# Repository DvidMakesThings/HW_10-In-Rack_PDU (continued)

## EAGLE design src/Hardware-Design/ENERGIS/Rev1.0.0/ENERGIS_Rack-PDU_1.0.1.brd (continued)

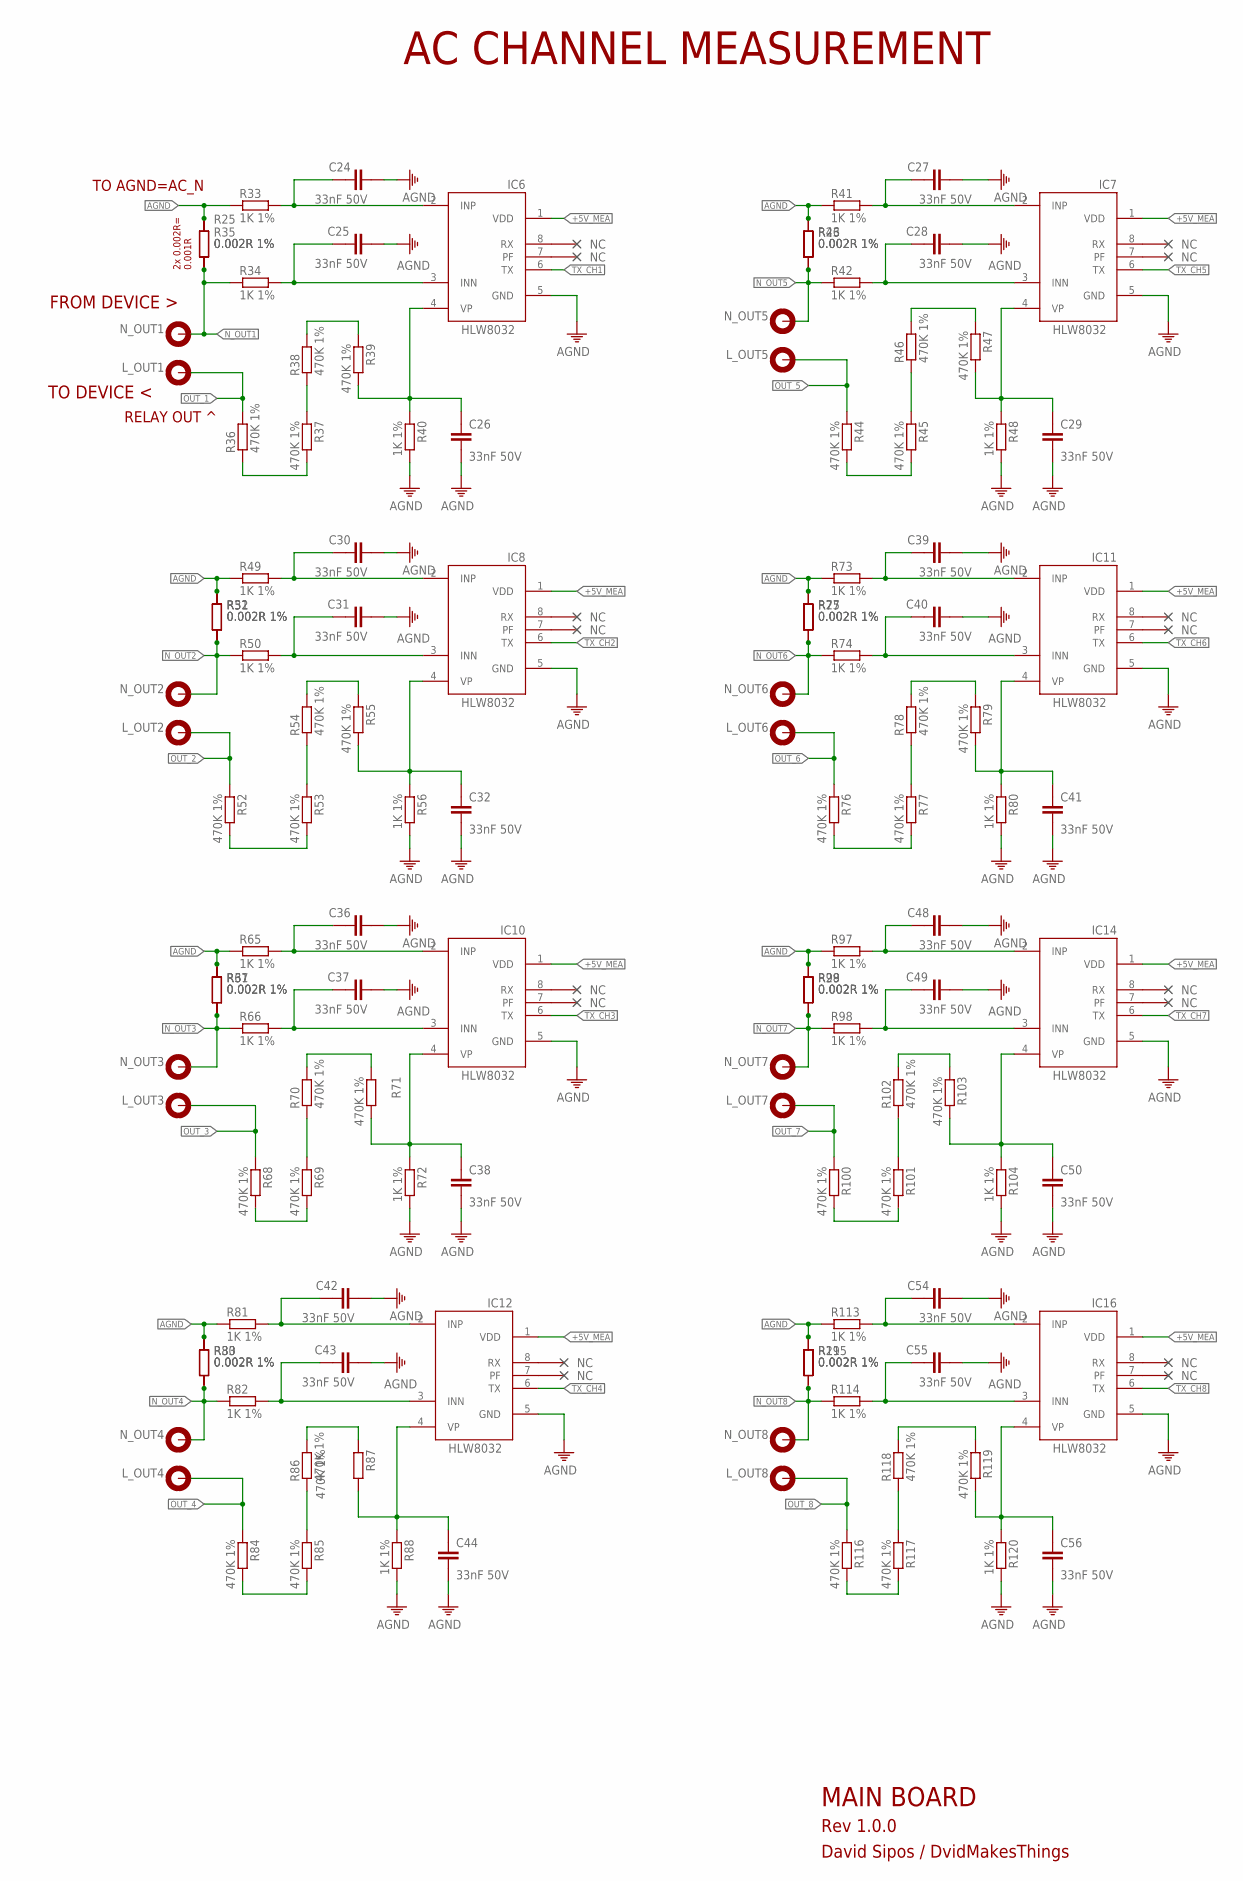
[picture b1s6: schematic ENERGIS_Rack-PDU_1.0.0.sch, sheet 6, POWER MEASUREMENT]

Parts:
C24, C25, C26, C27, C28, C29, C30, C31, C32, C36, C37, C38, C39, C40, C41, C42, C43, C44, C48, C49, C50, C54, C55, C56: 33nF 50V; 0805
IC6, IC7, IC8, IC10, IC11, IC12, IC14, IC16: HLW8032; SO8
L_OUT1, L_OUT2, L_OUT3, L_OUT4, L_OUT5, L_OUT6, L_OUT7, L_OUT8: MOUNT-PAD-ROUND2.8; 2,8-PAD
N_OUT1, N_OUT2, N_OUT3, N_OUT4, N_OUT5, N_OUT6, N_OUT7, N_OUT8: MOUNT-PAD-ROUND2.8; 2,8-PAD
R25, R26, R27, R28, R29, R30, R31, R32, R35, R43, R51, R67, R75, R83, R99, R115: 0.002R 1%; 2512
R33, R34, R40, R41, R42, R48, R49, R50, R56, R65, R66, R72, R73, R74, R80, R81, R82, R88, R97, R98, R104, R113, R114, R120: 1K 1%; 0805
R36, R37, R38, R39, R44, R45, R46, R47, R52, R53, R54, R55, R68, R69, R70, R71, R76, R77, R78, R79, R84, R85, R86, R87, R100, R101, R102, R103, R116, R117, R118, R119: 470K 1%; 0805

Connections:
+5V_MEA: IC6.1 (VDD), IC7.1 (VDD), IC8.1 (VDD), IC10.1 (VDD), IC11.1 (VDD), IC12.1 (VDD), IC14.1 (VDD), IC16.1 (VDD); also elsewhere on the board
AGND: C24.2, C25.2, C26.2, C27.2, C28.2, C29.2, C30.2, C31.2, C32.2, C36.2, C37.2, C38.2, C39.2, C40.2, C41.2, C42.2, C43.2, C44.2, C48.2, C49.2, C50.2, C54.2, C55.2, C56.2, IC6.5 (GND), IC7.5 (GND), IC8.5 (GND), IC10.5 (GND), IC11.5 (GND), IC12.5 (GND), IC14.5 (GND), IC16.5 (GND), R25.2, R26.2, R27.2, R28.2, R29.2, R30.2, R31.2, R32.2, R33.1, R35.2, R40.2, R41.1, R43.2, R48.2, R49.1, R51.2, R56.2, R65.1, R67.2, R72.2, R73.1, R75.2, R80.2, R81.1, R83.2, R88.2, R97.1, R99.2, R104.2, R113.1, R115.2, R120.2; also elsewhere on the board
unnamed: C24.1, IC6.2 (INP), R33.2
unnamed: C25.1, IC6.3 (INN), R34.2
unnamed: R38.2, R39.1
unnamed: R52.2, R53.2
unnamed: R37.1, R38.1
unnamed: C26.1, IC6.4 (VP), R39.2, R40.1
unnamed: C27.1, IC7.2 (INP), R41.2
unnamed: C28.1, IC7.3 (INN), R42.2
unnamed: R53.1, R54.1
unnamed: R54.2, R55.1
unnamed: R68.2, R69.2
unnamed: C29.1, IC7.4 (VP), R47.2, R48.1
unnamed: C30.1, IC8.2 (INP), R49.2
unnamed: C31.1, IC8.3 (INN), R50.2
unnamed: R69.1, R70.1
unnamed: R70.2, R71.1
unnamed: R84.2, R85.2
unnamed: C32.1, IC8.4 (VP), R55.2, R56.1
unnamed: C36.1, IC10.2 (INP), R65.2
unnamed: C37.1, IC10.3 (INN), R66.2
unnamed: R85.1, R86.1
unnamed: R86.2, R87.1
unnamed: R44.2, R45.2
unnamed: C38.1, IC10.4 (VP), R71.2, R72.1
unnamed: C39.1, IC11.2 (INP), R73.2
unnamed: C40.1, IC11.3 (INN), R74.2
unnamed: R45.1, R46.1
unnamed: R46.2, R47.1
unnamed: R76.2, R77.2
unnamed: C41.1, IC11.4 (VP), R79.2, R80.1
unnamed: C42.1, IC12.2 (INP), R81.2
unnamed: C43.1, IC12.3 (INN), R82.2
unnamed: R77.1, R78.1
unnamed: R78.2, R79.1
unnamed: R100.2, R101.2
unnamed: C44.1, IC12.4 (VP), R87.2, R88.1
unnamed: C48.1, IC14.2 (INP), R97.2
unnamed: C49.1, IC14.3 (INN), R98.2
unnamed: R101.1, R102.1
unnamed: R102.2, R103.1
unnamed: R116.2, R117.2
unnamed: C50.1, IC14.4 (VP), R103.2, R104.1
unnamed: C54.1, IC16.2 (INP), R113.2
unnamed: C55.1, IC16.3 (INN), R114.2
unnamed: R117.1, R118.1
unnamed: R118.2, R119.1
unnamed: C56.1, IC16.4 (VP), R119.2, R120.1
unnamed: R36.1, R37.2
N_OUT1: N_OUT1.B2,8, R25.1, R34.1, R35.1
N_OUT2: N_OUT2.B2,8, R32.1, R50.1, R51.1
N_OUT3: N_OUT3.B2,8, R31.1, R66.1, R67.1
N_OUT4: N_OUT4.B2,8, R30.1, R82.1, R83.1
N_OUT5: N_OUT5.B2,8, R26.1, R42.1, R43.1
N_OUT6: N_OUT6.B2,8, R27.1, R74.1, R75.1
N_OUT7: N_OUT7.B2,8, R28.1, R98.1, R99.1
N_OUT8: N_OUT8.B2,8, R29.1, R114.1, R115.1
OUT_1: L_OUT1.B2,8, R36.2; also elsewhere on the board
OUT_2: L_OUT2.B2,8, R52.1; also elsewhere on the board
OUT_3: L_OUT3.B2,8, R68.1; also elsewhere on the board
OUT_4: L_OUT4.B2,8, R84.1; also elsewhere on the board
OUT_5: L_OUT5.B2,8, R44.1; also elsewhere on the board
OUT_6: L_OUT6.B2,8, R76.1; also elsewhere on the board
OUT_7: L_OUT7.B2,8, R100.1; also elsewhere on the board
OUT_8: L_OUT8.B2,8, R116.1; also elsewhere on the board
TX_CH1: IC6.6 (TX); also elsewhere on the board
TX_CH2: IC8.6 (TX); also elsewhere on the board
TX_CH3: IC10.6 (TX); also elsewhere on the board
TX_CH4: IC12.6 (TX); also elsewhere on the board
TX_CH5: IC7.6 (TX); also elsewhere on the board
TX_CH6: IC11.6 (TX); also elsewhere on the board
TX_CH7: IC14.6 (TX); also elsewhere on the board
TX_CH8: IC16.6 (TX); also elsewhere on the board

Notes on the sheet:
AC CHANNEL MEASUREMENT
MAIN BOARD
Rev 1.0.0
David Sipos / DvidMakesThings
TO DEVICE <
FROM DEVICE >
2x 0.002R= 0.001R
TO AGND=AC_N
RELAY OUT ^

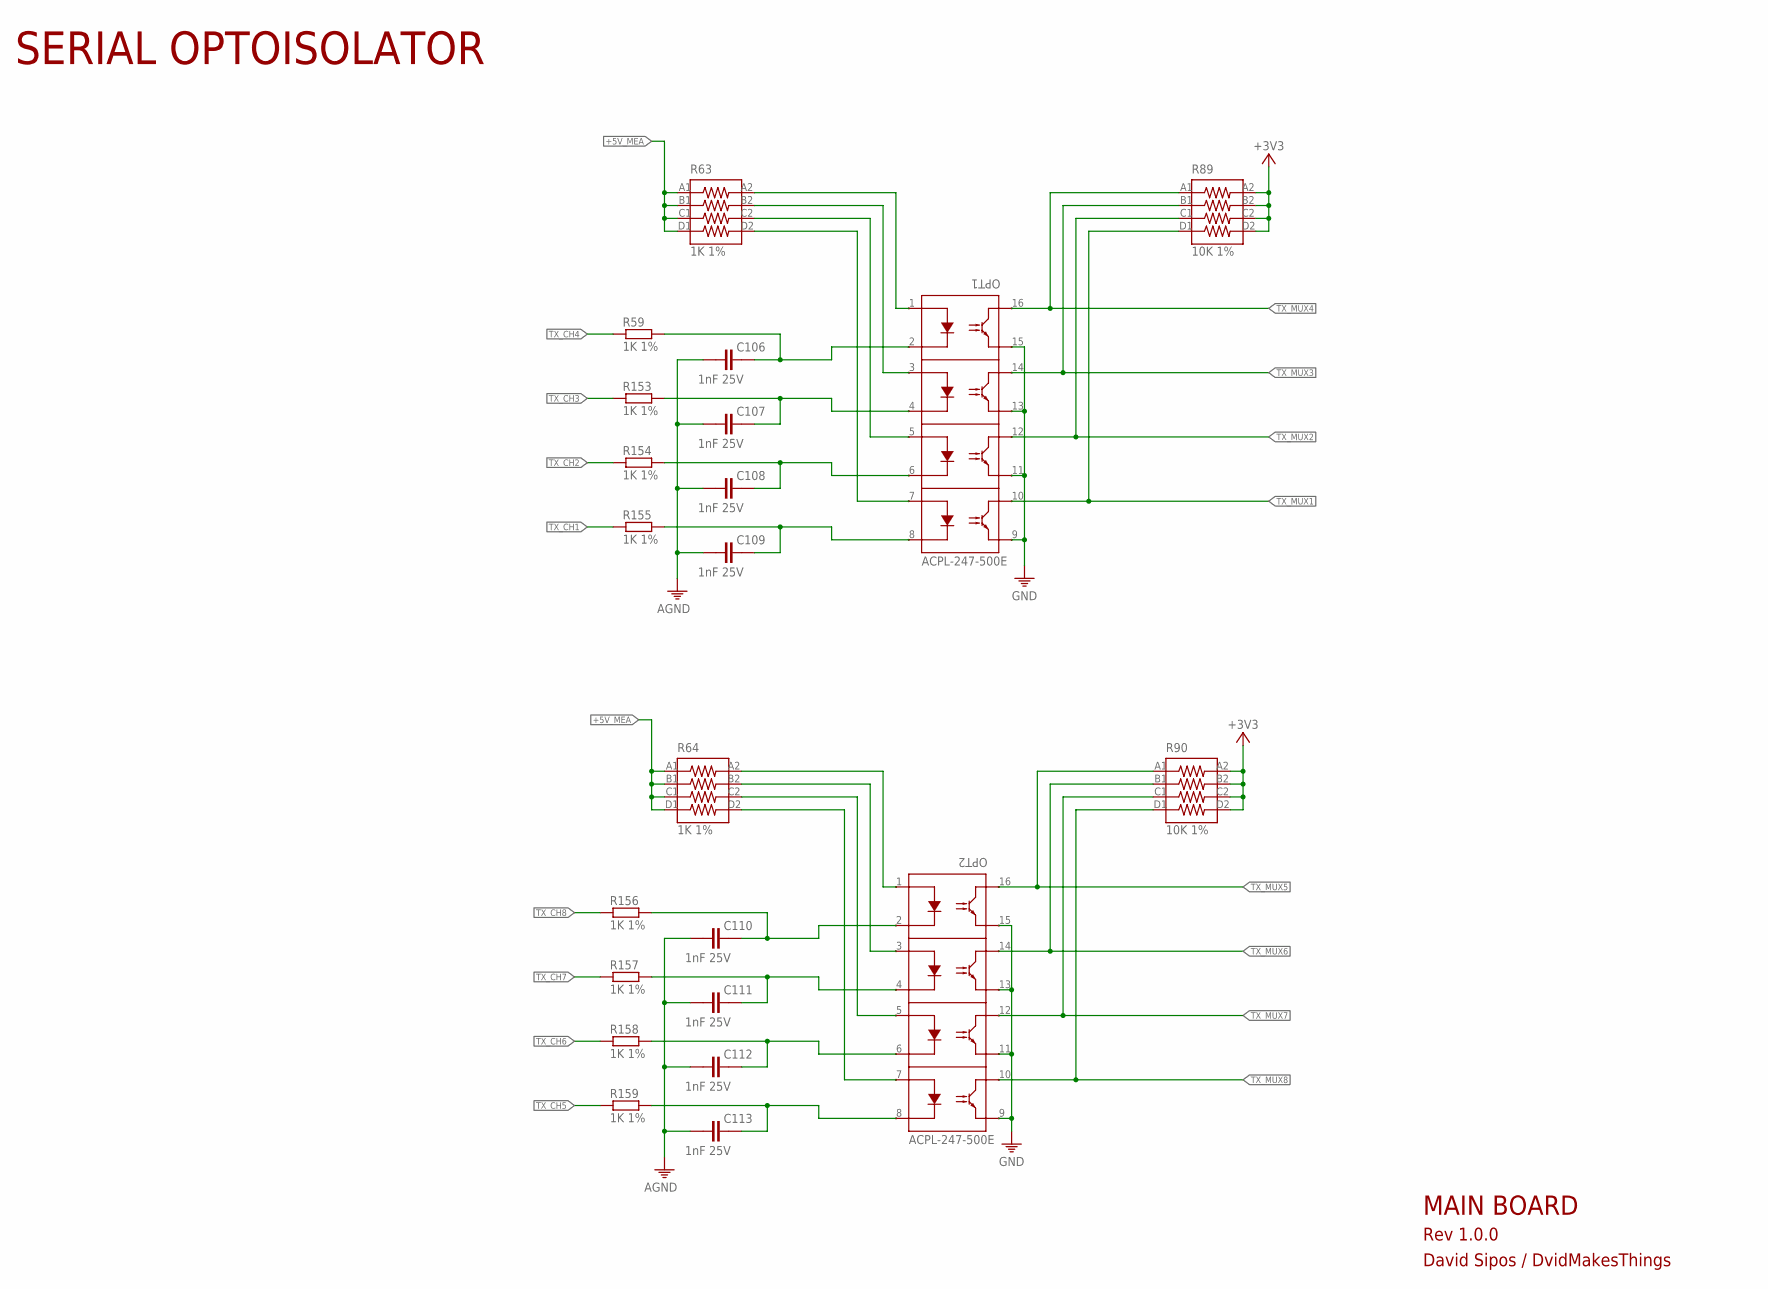
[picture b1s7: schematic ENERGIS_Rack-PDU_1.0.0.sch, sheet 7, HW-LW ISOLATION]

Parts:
C106, C107, C108, C109, C110, C111, C112, C113: 1nF 25V; 0201
OPT1, OPT2: ACPL-247-500E; SO16
R59, R153, R154, R155, R156, R157, R158, R159: 1K 1%; 0201
R63, R64: 1K 1%; _0603X4-1206
R89, R90: 10K 1%; _0603X4-1206

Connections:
+3V3: R89.A2 (8), R89.B2 (7), R89.C2 (6), R89.D2 (5), R90.A2 (8), R90.B2 (7), R90.C2 (6), R90.D2 (5); also elsewhere on the board
+5V_MEA: R63.A1 (1), R63.B1 (2), R63.C1 (3), R63.D1 (4), R64.A1 (1), R64.B1 (2), R64.C1 (3), R64.D1 (4); also elsewhere on the board
AGND: C106.2, C107.2, C108.2, C109.2, C110.2, C111.2, C112.2, C113.2; also elsewhere on the board
GND: OPT1.9, OPT1.11, OPT1.13, OPT1.15, OPT2.9, OPT2.11, OPT2.13, OPT2.15; also elsewhere on the board
TX1_LP: C109.1, OPT1.8, R155.2
TX1_PU: OPT1.7, R63.D2 (5)
TX2_LP: C108.1, OPT1.6, R154.2
TX2_PU: OPT1.5, R63.C2 (6)
TX3_LP: C107.1, OPT1.4, R153.2
TX3_PU: OPT1.3, R63.B2 (7)
TX4_LP: C106.1, OPT1.2, R59.2
TX4_PU: OPT1.1, R63.A2 (8)
TX5_LP: C110.1, OPT2.2, R156.2
TX5_PU: OPT2.1, R64.A2 (8)
TX6_LP: C111.1, OPT2.4, R157.2
TX6_PU: OPT2.3, R64.B2 (7)
TX7_LP: C112.1, OPT2.6, R158.2
TX7_PU: OPT2.5, R64.C2 (6)
TX8_LP: C113.1, OPT2.8, R159.2
TX8_PU: OPT2.7, R64.D2 (5)
TX_CH1: R155.1; also elsewhere on the board
TX_CH2: R154.1; also elsewhere on the board
TX_CH3: R153.1; also elsewhere on the board
TX_CH4: R59.1; also elsewhere on the board
TX_CH5: R159.1; also elsewhere on the board
TX_CH6: R158.1; also elsewhere on the board
TX_CH7: R157.1; also elsewhere on the board
TX_CH8: R156.1; also elsewhere on the board
TX_MUX1: OPT1.10, R89.D1 (4); also elsewhere on the board
TX_MUX2: OPT1.12, R89.C1 (3); also elsewhere on the board
TX_MUX3: OPT1.14, R89.B1 (2); also elsewhere on the board
TX_MUX4: OPT1.16, R89.A1 (1); also elsewhere on the board
TX_MUX5: OPT2.16, R90.A1 (1); also elsewhere on the board
TX_MUX6: OPT2.14, R90.B1 (2); also elsewhere on the board
TX_MUX7: OPT2.12, R90.C1 (3); also elsewhere on the board
TX_MUX8: OPT2.10, R90.D1 (4); also elsewhere on the board

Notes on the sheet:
MAIN BOARD
Rev 1.0.0
David Sipos / DvidMakesThings
SERIAL OPTOISOLATOR

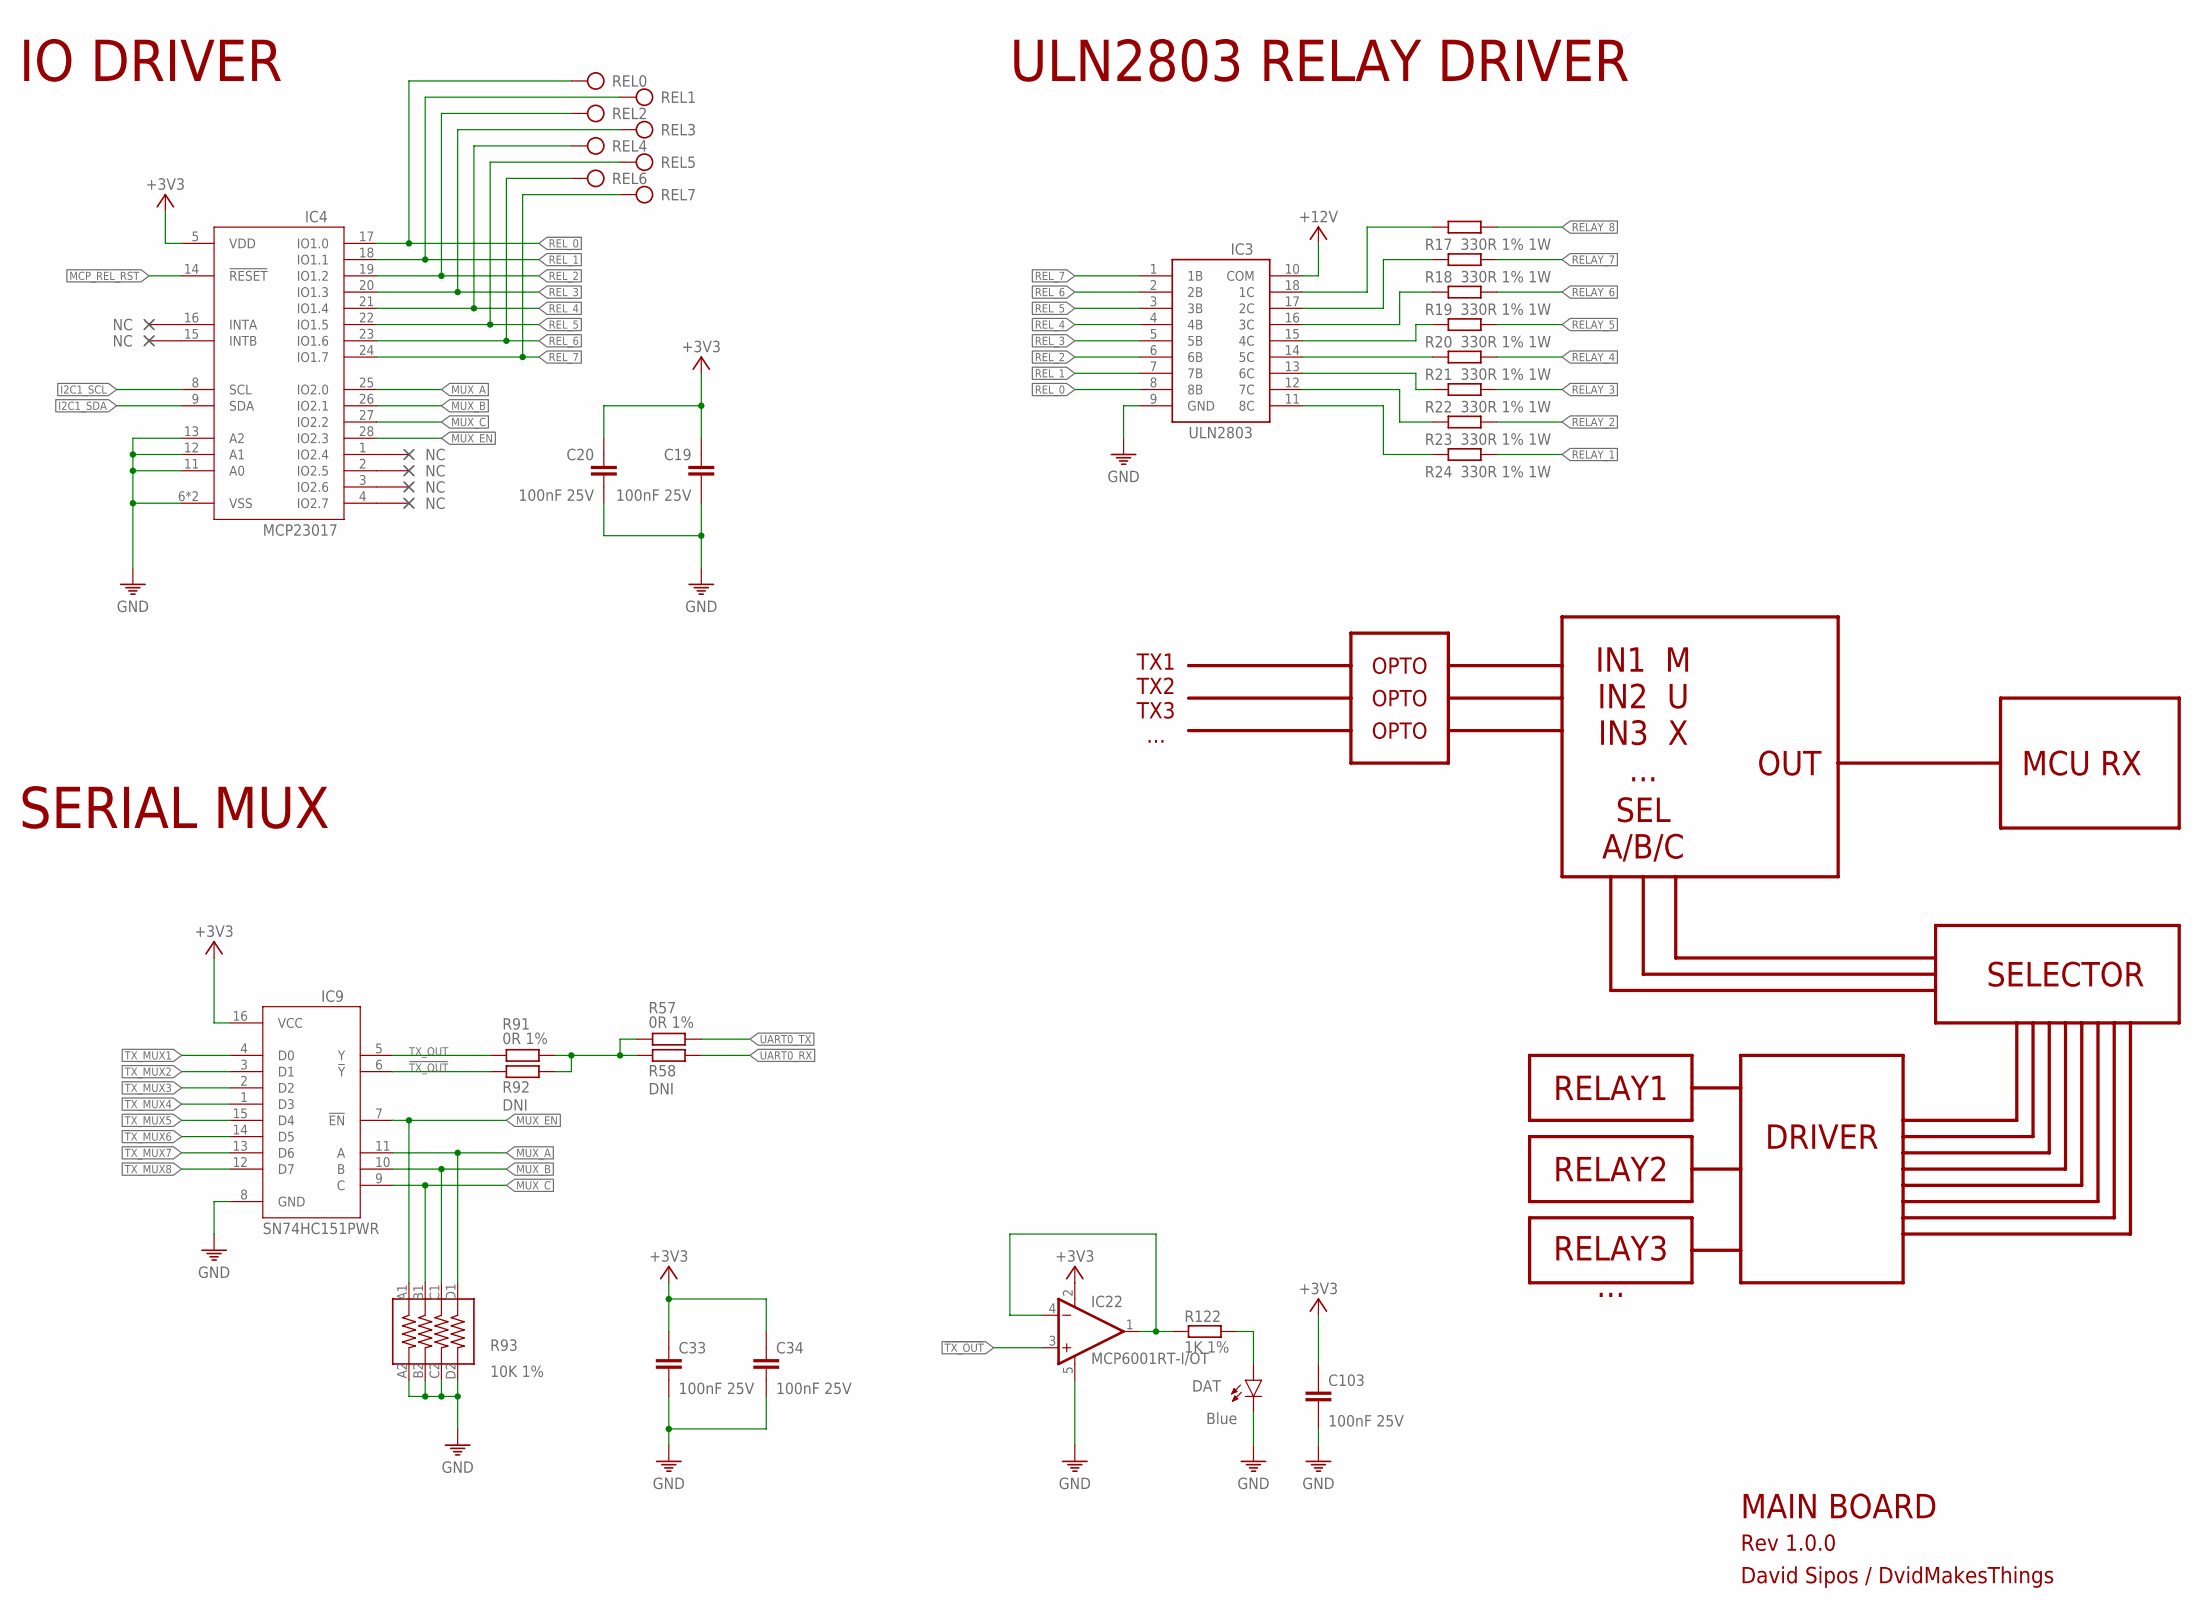
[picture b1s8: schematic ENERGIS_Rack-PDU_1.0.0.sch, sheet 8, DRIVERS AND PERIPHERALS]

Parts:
C19, C20, C33, C34: 100nF 25V; 0402
C103: 100nF 25V; 0201
DAT: Blue; LED-0603
IC3: ULN2803AFWG; SO18
IC4: MCP23017T-E/ML; QFN28[6X6]ML
IC9: SN74HC151PWR; TSSOP16
IC22: MCP6001RT-I/OT; SOT23-5
R17, R18, R19, R20, R21, R22, R23, R24: 330R 1% 1W; 2512
R57, R91: 0R 1%; 0402
R58, R92: DNI; 0402
R93: 10K 1%; _0603X4-1206
R122: 1K 1%; 0402
REL0, REL1, REL2, REL3, REL4, REL5, REL6, REL7: TP

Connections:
!TX_OUT: IC9.6 (!Y), IC22.3 (+IN), R92.1
+3V3: C19.1, C20.1, C33.1, C34.1, C103.1, IC4.5 (VDD), IC9.16 (VCC), IC22.2 (V+); also elsewhere on the board
+12V: IC3.10 (COM); also elsewhere on the board
GND: C19.2, C20.2, C33.2, C34.2, C103.2, DAT.C, IC3.9 (GND), IC4.6 (VSS), IC4.11 (A0), IC4.12 (A1), IC4.13 (A2), IC4.PAD (VSS), IC9.8 (GND), IC22.5 (V-), R93.A2 (8), R93.B2 (7), R93.C2 (6), R93.D2 (5); also elsewhere on the board
I2C1_SCL: IC4.8 (SCL); also elsewhere on the board
I2C1_SDA: IC4.9 (SDA); also elsewhere on the board
MCP_REL_RST: IC4.14 (!RESET); also elsewhere on the board
MUX_A: IC4.25 (IO2.0), IC9.11 (A), R93.D1 (4)
MUX_B: IC4.26 (IO2.1), IC9.10 (B), R93.C1 (3)
MUX_C: IC4.27 (IO2.2), IC9.9 (C), R93.B1 (2)
MUX_EN: IC4.28 (IO2.3), IC9.7 (!EN), R93.A1 (1)
unnamed: DAT.A, R122.2
unnamed: IC3.14 (5C), R21.1
unnamed: IC3.11 (8C), R24.1
unnamed: IC3.12 (7C), R23.1
unnamed: IC3.13 (6C), R22.1
unnamed: IC3.15 (4C), R20.1
unnamed: IC3.16 (3C), R19.1
unnamed: IC3.17 (2C), R18.1
unnamed: IC3.18 (1C), R17.1
RELAY_1: R24.2; also elsewhere on the board
RELAY_2: R23.2; also elsewhere on the board
RELAY_3: R22.2; also elsewhere on the board
RELAY_4: R21.2; also elsewhere on the board
RELAY_5: R20.2; also elsewhere on the board
RELAY_6: R19.2; also elsewhere on the board
RELAY_7: R18.2; also elsewhere on the board
RELAY_8: R17.2; also elsewhere on the board
REL_0: IC3.8 (8B), IC4.17 (IO1.0), REL0.TP
REL_1: IC3.7 (7B), IC4.18 (IO1.1), REL1.TP
REL_2: IC3.6 (6B), IC4.19 (IO1.2), REL2.TP
REL_3: IC3.5 (5B), IC4.20 (IO1.3), REL3.TP
REL_4: IC3.4 (4B), IC4.21 (IO1.4), REL4.TP
REL_5: IC3.3 (3B), IC4.22 (IO1.5), REL5.TP
REL_6: IC3.2 (2B), IC4.23 (IO1.6), REL6.TP
REL_7: IC3.1 (1B), IC4.24 (IO1.7), REL7.TP
TX_FB: IC22.1 (OUT), IC22.4 (-IN), R122.1
TX_MUX1: IC9.4 (D0); also elsewhere on the board
TX_MUX2: IC9.3 (D1); also elsewhere on the board
TX_MUX3: IC9.2 (D2); also elsewhere on the board
TX_MUX4: IC9.1 (D3); also elsewhere on the board
TX_MUX5: IC9.15 (D4); also elsewhere on the board
TX_MUX6: IC9.14 (D5); also elsewhere on the board
TX_MUX7: IC9.13 (D6); also elsewhere on the board
TX_MUX8: IC9.12 (D7); also elsewhere on the board
TX_OUT: IC9.5 (Y), R91.1
TX_OUTSEL: R57.1, R58.1, R91.2, R92.2
UART0_RX: R58.2; also elsewhere on the board
UART0_TX: R57.2; also elsewhere on the board

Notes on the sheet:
ULN2803 RELAY DRIVER
IO DRIVER
SERIAL MUX
MAIN BOARD
Rev 1.0.0
David Sipos / DvidMakesThings
TX1 TX2 TX3 ...
OPTO
IN1 M IN2 U IN3 X ...
SELECTOR
SEL A/B/C
OUT
MCU RX
RELAY1
RELAY2
RELAY3 ...
DRIVER

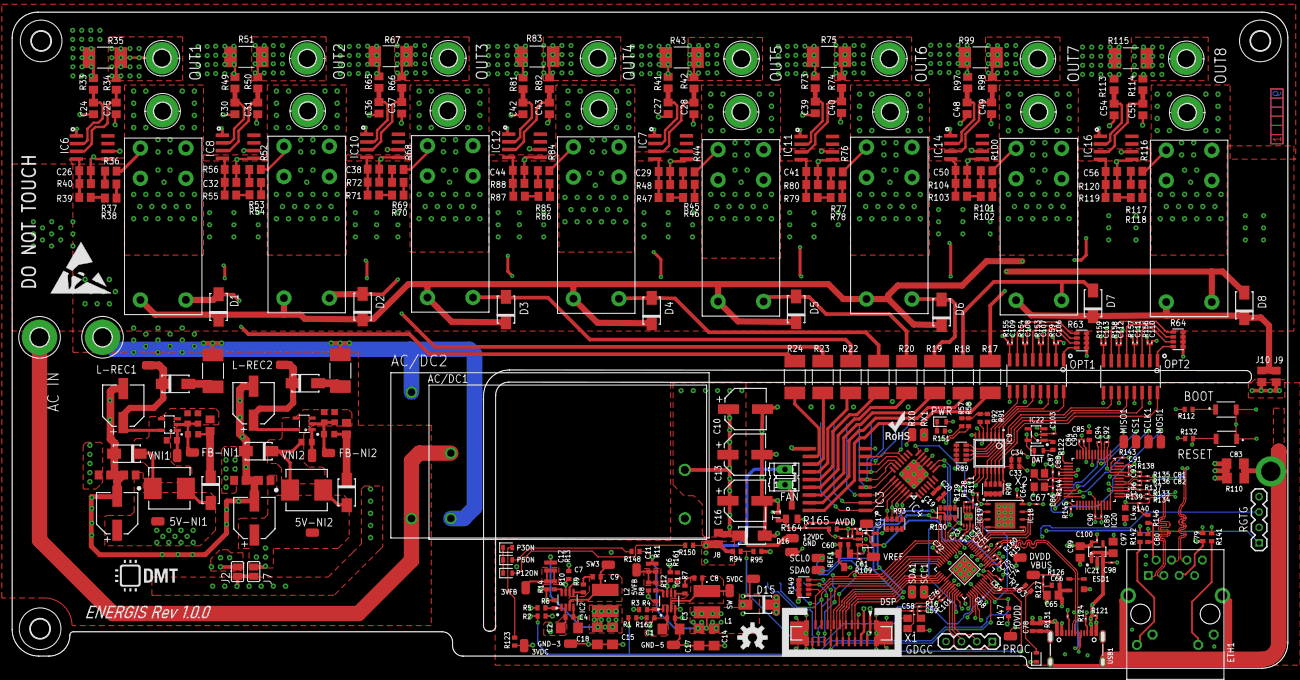
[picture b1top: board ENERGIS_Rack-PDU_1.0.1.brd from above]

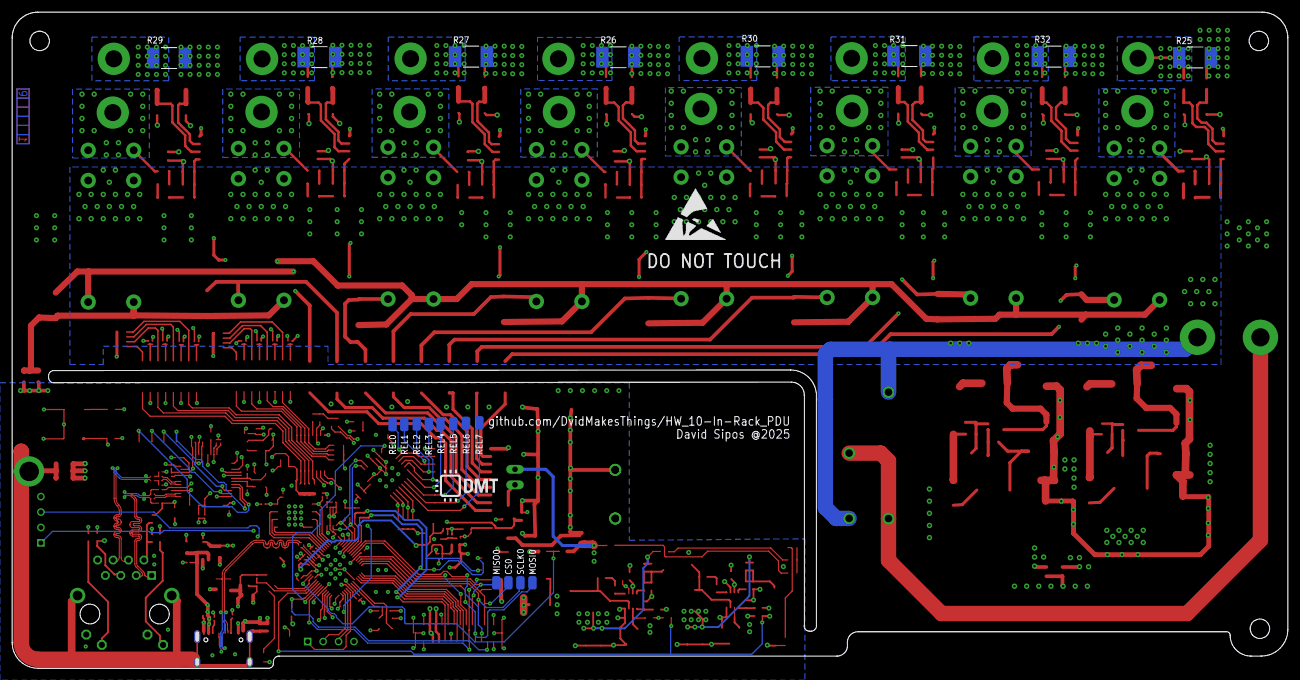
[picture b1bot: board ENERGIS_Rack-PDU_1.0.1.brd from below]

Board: 6 copper layers, 210.0 x 108.0 mm, 428 parts (22 on the bottom side), 251 nets.

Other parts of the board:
U$1, U$2: ESD_10.00
U$3, U$4, U$6: 3,2
U$5, U$7: DMT
U$10: OSHW-LOGO-M
U$11: ROHS_LOGO_0.18_IN

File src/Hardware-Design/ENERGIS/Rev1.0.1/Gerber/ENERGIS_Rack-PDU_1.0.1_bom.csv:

Comment,Designator,Footprint,LCSC Part #
0.002R 1%,R25 R26 R27 R28 R29 R30 R31 R32 R35 R43 R51 R67 R75 R83 R99 R115,2512,C728320
0R 1%,J8 J9 J10,0805,C17477
0R 1%,R57 R91,0402,C17168
1K 1%,R16,0201,C270365
1K 1%,R33 R34 R40 R41 R42 R48 R49 R50 R56,0805,C17513
1K 1%,R59,0201,C270365
1K 1%,R63 R64,_0603X4-1206,C110021
1K 1%,R65 R66 R72 R73 R74 R80 R81 R82 R88 R97 R98 R104,0805,C17513
1K 1%,R112,0402,C11702
1K 1%,R113 R114 R120,0805,C17513
1K 1%,R122 R123 R151,0402,C11702
1K 1%,R153 R154 R155 R156 R157 R158 R159,0201,C270365
1K 1%,R163,0402,C11702
1M 1%,R110,1206,C17927
1M 1%,R131,0402,C26083
1M 1%,R144,0201,C295786
1N4007,D9 D10 D12 D13,SMA/DO-214AC,C727081
1mH,L3 L5,L-6.6X6.6,C168049
1nF 25V,C106 C107 C108 C109 C110 C111 C112 C113,0201,C7694325V
1nF 50V,C5 C51,0603,C1588
1uF 16V,C102,0201,C307385
1uF 25V,C60 C104,0402,C52923
1uF 50V,C45 C57,0805,C28323
2.2K 1%,R121,0201,C473508
2.2uF 50V,C21 C46,0603,C913904
2.2uF 400V,C35 C47,6.3X7.7(DXL),C3345109
2.4K 1%,R148,0402,C25882
3.3K 1%,R130 R149,_0603X4-1206,C1734380
3.3R 1%,R133 R134 R135 R136,0201,C158547
4.2uH,L2,SRR5228A,
4.7K 1%,R109 R129 R145,0201,C270346
4.7nF 50V,C78,0402,C1538
4.7uF 25V,C85,0402,C22367824
4.9uH,L1,SRR5228A,
4.99K 1%,R60 R61 R105 R107,0603,C23046
5.1K 1%,R124 R125,0201,C274341
6.8nF 50V,C81 C82,0201,C285015
7.5K 1%,R6 R12,0402,C25918
8.2K 1%,R150,0402,C25924
9.09K 1%,R4,0402,C11549
10K 1%,R2,0402,C25744
10K 1%,R89 R90 R93,_0603X4-1206,C110924
10K 1%,R95,0402,C25744
10K 1%,R96 R108,0805,C17414
10K 1%,R126 R127,0201,C473048
10K 1%,R132 R147 R162 R164,0402,C25744
10R 1%,R7 R9,0402,C25077
10R 1%,R152,0201,C270817
10uF 50V,C65 C97 C99,0805,C440198
12.4K 1%,R143,R0201,
12.7K 1%,R14,0402,C25853
15pF 50V,C58 C59,0201,C22374851
18pF 50V,C86 C87,0201,C62164
20K 1%,R8,0402,C25765
22nF 50V,C80,0402,C1532
22uF 25V,C1 C2 C14 C15 C17 C18,1206,C12891
25MHz,X2,WE-XTAL_CFPX-180,C9006
27R 1%,R15 R160,0201,C473051
33K,R10,0402,
33nF 50V,C24 C25 C26 C27 C28 C29 C30 C31 C32 C36 C37 C38 C39 C40 C41 C42 C43 C44 C48 C49 C50 C54 C55 C56,0805,C107150
33pF 50V,C11 C12,0402,C107005
39R 1% 2W,R62 R106,2512,C175263
40.2K 1%,R11 R13,0402,C25893
49.9R 1%,R137 R138 R139 R140,0201,C155744
100K 1%,R3 R5 R94,0402,C25741
100nF 25V,C3 C4 C6 C7 C8 C9 C19 C20 C33 C34,0402,C56392
100nF 25V,C61 C62 C63 C64,0201,C76939
100nF 25V,C66,0402,C56392
100nF 25V,C67 C68 C69 C70 C71 C72 C73 C74 C75 C76 C77,0201,C76939
100nF 25V,C79,0402,C56392
100nF 25V,C84 C88 C89 C90 C91 C92 C93 C94 C95 C96 C98 C100 C101 C103,0201,C76939
100uF 25V,C10 C13 C16,6.3X7.7(DXL),C267469
100uF 50V,C23 C53,6.3X7.7(DXL),C3151829
220nF 50V,C22 C52,0805,C5378
330R 1% 1W,R17 R18 R19 R20 R21 R22 R23 R24,2512,C620880
470K 1%,R36 R37 R38 R39 R44 R45 R46 R47 R52 R53 R54 R55 R68 R69 R70 R71 R76 R77 R78 R79 R84 R85 R86 R87 R100 R101 R102 R103 R116 R117 R118 R119,0805,C17709
470R 1%,R141 R142 R146,0402,C25117
ABM8-272-T3 12MHz,X1,WE-XTAL_CFPX-180,C20625731
ACPL-247-500E ,OPT1 OPT2,SO16,C188681
AFC11-S20ICC-00 ,DSP,FPC20,C11073
B3U-1000P ,BOOT RESET,B3U-1000P,C231329
BLM18EG221TN1D,L4,0603,C113025
Blue,DAT,LED-0603,C965807
C1206C102KGRACTM,C83,C1206,
CAT24C256HU4IGT3,IC19,SON50P300X200X50-9T130X140N,C233771
DNI,R1 R58 R92,0402,
DNI,R111,R0201,
DNI,R161,0402,
G2RL-1A-E DC12 ,K1 K2 K3 K4 K5 K6 K7 K8,RELAY_G2RL-1A-E_DC5_OMR,C1564126
Green,P3ON P5ON P12ON PROC PWR,LED-0603,C965804
HLW8032,IC6 IC7 IC8 IC10 IC11 IC12 IC14 IC16,SO8,C128023
IRM-10-15 ,AC/DC2,IRM_15_12,C5439799
IRM_10_12,AC/DC1,IRM_10_12,C20618065
J1B1211CCD,ETH1,J1B1211CCD,C910371
JP,J2 J7,SJ,
LM4040B30FTA,REF1,SOT23,C460604
MBRA340T3G,D1 D2 D3 D4 D5 D6 D7 D8,SMA/DO-214AC,C26178
MCP6001RT-I/OT,IC17 IC22,SOT23-5,C154973
MCP23017T-E/ML ,IC4,QFN28[6X6]ML,C629439
MIC5504-3.3YM5 ,IC21,SOT23-5,C41348078
MOUNT-PAD-ROUND2.8,L_OUT1,2 8-PAD,
MOUNT-PAD-ROUND2.8,L_OUT2,2 8-PAD,
MOUNT-PAD-ROUND2.8,L_OUT3,2 8-PAD,
MOUNT-PAD-ROUND2.8,L_OUT4,2 8-PAD,
MOUNT-PAD-ROUND2.8,L_OUT5,2 8-PAD,
MOUNT-PAD-ROUND2.8,L_OUT6,2 8-PAD,
MOUNT-PAD-ROUND2.8,L_OUT7,2 8-PAD,
MOUNT-PAD-ROUND2.8,L_OUT8,2 8-PAD,
MOUNT-PAD-ROUND2.8,N_OUT1,2 8-PAD,
MOUNT-PAD-ROUND2.8,N_OUT2,2 8-PAD,
MOUNT-PAD-ROUND2.8,N_OUT3,2 8-PAD,
MOUNT-PAD-ROUND2.8,N_OUT4,2 8-PAD,
MOUNT-PAD-ROUND2.8,N_OUT5,2 8-PAD,
MOUNT-PAD-ROUND2.8,N_OUT6,2 8-PAD,
MOUNT-PAD-ROUND2.8,N_OUT7,2 8-PAD,
MOUNT-PAD-ROUND2.8,N_OUT8,2 8-PAD,
MOUNT-PAD-ROUND3.0,AC_L,3 0-PAD,
MOUNT-PAD-ROUND3.0,AC_N,3 0-PAD,
MP150GJ,IC5 IC13,SOT23-5,
MP2315GJ-Z ,IC1 IC2,SOT65P280X110-8N,C45889
NC,R128 R165,R0201,
RP2040,IC15,QFN56,C2040
SMAJ15A,D16,SMA/DO-214AC,C23424
SN74HC151PWR,IC9,TSSOP16,C2653837
SP0503BAHTG,ESD1,SOT143,C3040626
SS12,D15,SMA/DO-214AC,C727049
TP,3VDC 3VFB 5V-NI1 5V-NI2 5VDC 5VFB 12VDC AVDD CS0 CS1 DVDD FB-NI1 FB-NI2 GND GND-3 GND-5 IOVDD L-REC1 L-REC2 MISO0 MISO1 MOSI0 MOSI1 REL0 REL1 REL2 REL3 REL4 REL5 REL6 REL7 RX0 RX1 SCL0 SCL1 SCLK0 SCLK1 SDA0 SDA1 SW SW3 VBUS VNI1 VNI2 VREF,TP,
ULN2803AFWG,IC3,SO18,C845537
US1J-E3/61T ,D11 D14,SMA/DO-214AC,C44763
USB-TYPE-C-018 ,USB1,USB-C,C2927038
W25Q128JVPIQ,IC18,SON127P600X500X75-8N,C190862
W5500,IC20,LQFP48,C32843

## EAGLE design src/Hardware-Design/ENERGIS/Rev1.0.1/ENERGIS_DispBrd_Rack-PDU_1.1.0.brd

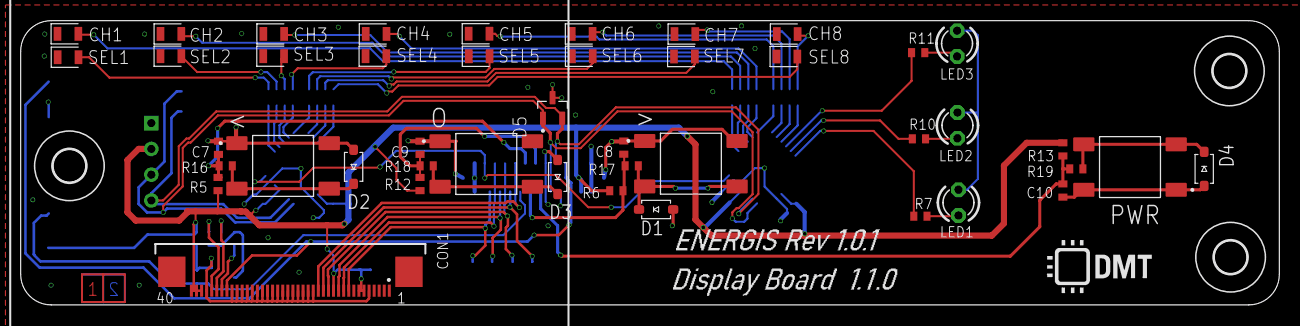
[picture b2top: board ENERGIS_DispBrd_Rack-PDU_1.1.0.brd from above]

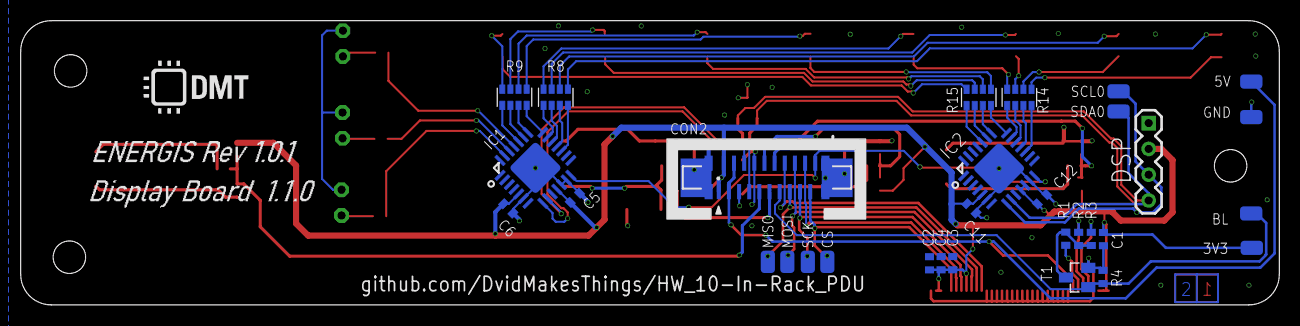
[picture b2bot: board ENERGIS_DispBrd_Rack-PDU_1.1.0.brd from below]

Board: 2 copper layers, 124.0 x 28.0 mm, 80 parts (32 on the bottom side), 63 nets.

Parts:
3V3, 5V: TP
<: TS-1002S-04326C; PUSHBUTTON-6X6
>: TS-1002S-04326C; PUSHBUTTON-6X6
BL: TP
C1, C2, C3, C4: DNI; C0402
C5, C6, C7, C8, C9, C10, C11, C12: 100nF 50V; 0402
CH1, CH2, CH3, CH4, CH5, CH6, CH7, CH8: Green; LED-0805
CON1: DNI; FPC40_3.5TFT
CON2: AFC11-S20ICC-00; FPC20
CS: TP
D1, D2, D3, D4: PTVS3V3S1UR,115; SOD-123
D5: RCLAMP0582BQTCT; SOT-523
DSP: DNI; 1X4
GND: TP
IC1, IC2: MCP23017T-E/ML; QFN28[6X6]ML
LED1: GREEN; LED3MM
LED2: BLUE; LED3MM
LED3: RED; LED3MM
MISO: TP
MOSI: TP
O: TS-1002S-04326C; PUSHBUTTON-6X6
PWR: TS-1002S-04326C; PUSHBUTTON-6X6
R1, R2, R3: DNI; 0402
R4, R16, R17, R18, R19: 10K 1%; 0402
R5, R6, R12, R13: 33K 1%; 0402
R7, R10, R11: 1K 1%; 0402
R8, R9, R14, R15: 1K 1%; _0603X4-1206
SCK: TP
SCL0: TP
SDA0: TP
SEL1, SEL2, SEL3, SEL4, SEL5, SEL6, SEL7, SEL8: Orange; LED-0805
T1: BSS138; SOT23
U$1, U$5: DMT
U$2, U$3, U$4: 3,2

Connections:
+3V3: 3V3.TP, C1.1, C2.1, C3.1, C4.1, C5.1, C6.1, C11.1, C12.1, CON1.6, CON1.7, CON1.12, CON1.38, CON1.39, CON1.40, CON2.1, CON2.2, DSP.2, IC1.5, IC1.11, IC2.5, IC2.11, IC2.12, R5.1, R6.1, R12.1, R13.1
+5V: 5V.TP, CON1.33, CON2.3, CON2.4
GND: <.1, <.2, >.1, >.2, C1.2, C2.2, C3.2, C4.2, C5.2, C6.2, C7.2, C8.2, C9.2, C10.2, C11.2, C12.2, CH1.C, CH2.C, CH3.C, CH4.C, CH5.C, CH6.C, CH7.C, CH8.C, CON1.5, CON1.16, CON1.17, CON1.18, CON1.19, CON1.20, CON1.21, CON1.22, CON1.23, CON1.24, CON1.25, CON1.26, CON1.27, CON1.28, CON1.29, CON1.30, CON1.31, CON1.32, CON1.37, CON1.Z1, CON1.Z2, CON2.5, CON2.8, CON2.Z0, CON2.Z1, CON2.Z2, CON2.Z3, CON2.Z4, CON2.Z5, D1.A, D2.A, D3.A, D4.A, D5.3, DSP.1, GND.TP, IC1.6, IC1.12, IC1.13, IC1.PAD, IC2.6, IC2.13, IC2.PAD, LED1.K, LED2.K, LED3.K, O.1, O.2, PWR.1, PWR.2, R4.2, SEL1.C, SEL2.C, SEL3.C, SEL4.C, SEL5.C, SEL6.C, SEL7.C, SEL8.C, T1.2
I2C0_SCL: CON2.7, D5.1, DSP.3, IC1.8, IC2.8, SCL0.TP
I2C0_SDA: CON2.6, D5.2, DSP.4, IC1.9, IC2.9, SDA0.TP
KEY_0: C7.1, CON2.12, R5.2, R16.2
KEY_1: C8.1, CON2.11, R6.2, R17.2
KEY_2: C9.1, CON2.10, R12.2, R18.2
KEY_3: C10.1, CON2.9, R13.2, R19.2
LCD_BL: BL.TP, CON2.13, R4.1, T1.1
LCD_CS: CON1.9, CON2.19, CS.TP
LCD_DC: CON1.10, CON2.18
LCD_MISO: CON1.14, CON2.15, MISO.TP
LCD_MOSI: CON1.13, CON2.16, MOSI.TP
LCD_RES: CON1.15, CON2.14
LCD_SCLK: CON1.11, CON2.17, SCK.TP
MCP_LCD_RST: CON2.20, IC1.14, IC2.14
unnamed: CON1.35, R2.2
unnamed: CON1.36, R3.2
unnamed: R1.1, R2.1, R3.1, T1.3
unnamed: CON1.34, R1.2
unnamed: <.3, <.4, D2.C, R16.1
unnamed: IC2.17, R14.D1
unnamed: IC2.18, R14.C1
unnamed: IC2.19, R14.B1
unnamed: IC2.20, R14.A1
unnamed: IC2.21, R15.D1
unnamed: IC2.22, R15.C1
unnamed: IC2.23, R15.B1
unnamed: IC2.24, R15.A1
unnamed: R14.D2, SEL1.A
unnamed: R14.C2, SEL2.A
unnamed: R14.B2, SEL3.A
unnamed: R14.A2, SEL4.A
unnamed: R15.D2, SEL5.A
unnamed: R15.C2, SEL6.A
unnamed: R15.B2, SEL7.A
unnamed: R15.A2, SEL8.A
unnamed: D3.C, O.3, O.4, R18.1
unnamed: D4.C, PWR.3, PWR.4, R19.1
unnamed: >.3, >.4, D1.C, R17.1
unnamed: IC1.26, R10.1
unnamed: IC1.27, R7.1
unnamed: IC1.25, R11.1
unnamed: IC1.17, R8.D1
unnamed: IC1.18, R8.C1
unnamed: IC1.19, R8.B1
unnamed: IC1.20, R8.A1
unnamed: IC1.21, R9.D1
unnamed: IC1.22, R9.C1
unnamed: IC1.23, R9.B1
unnamed: IC1.24, R9.A1
unnamed: CH1.A, R8.D2
unnamed: CH2.A, R8.C2
unnamed: CH3.A, R8.B2
unnamed: CH4.A, R8.A2
unnamed: CH5.A, R9.D2
unnamed: CH6.A, R9.C2
unnamed: CH7.A, R9.B2
unnamed: CH8.A, R9.A2
unnamed: LED3.A, R11.2
unnamed: LED2.A, R10.2
unnamed: LED1.A, R7.2

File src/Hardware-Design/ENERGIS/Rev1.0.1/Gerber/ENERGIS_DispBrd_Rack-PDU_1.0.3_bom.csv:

Comment,Designator,Footprint,LCSC Part #
1K 1%,R7,0402,C11702
1K 1%,R8 R9,_0603X4-1206,C110021
1K 1%,R10 R11,0402,C11702
1K 1%,R14 R15,_0603X4-1206,C110021
10K 1%,R4 R5 R6 R12 R13,0402,C25744
100nF 50V,C5 C6 C7 C8 C9 C10 C11 C12,0402,C307331
AFC11-S20ICC-00 ,CON2,FPC20,C11073
BLUE,LED2,LED3MM,C86881
BSS138,T1,SOT23,
DNI,C1 C2 C3 C4,C0402,
DNI,CON1,FPC40_3.5TFT,
DNI,DSP,1X4,
DNI,R1 R2 R3,0402,
GREEN,LED1,LED3MM,C414645
Green,CH1 CH2 CH3 CH4 CH5 CH6 CH7 CH8,LED-0805,C2297
MCP23017T-E/ML ,IC1 IC2,QFN28[6X6]ML,C629439
Orange,SEL1 SEL2 SEL3 SEL4 SEL5 SEL6 SEL7 SEL8,LED-0805,C434437
RED,LED3,LED3MM,C330752
TP,3V3 5V BL CS GND MISO MOSI SCK SCL0 SDA0,TP,
TS-1002S-04326C ,< > O PWR,PUSHBUTTON-6X6,C455108
